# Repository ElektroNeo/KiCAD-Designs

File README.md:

# KiCAD-Designs
Useful KiCAD designs.

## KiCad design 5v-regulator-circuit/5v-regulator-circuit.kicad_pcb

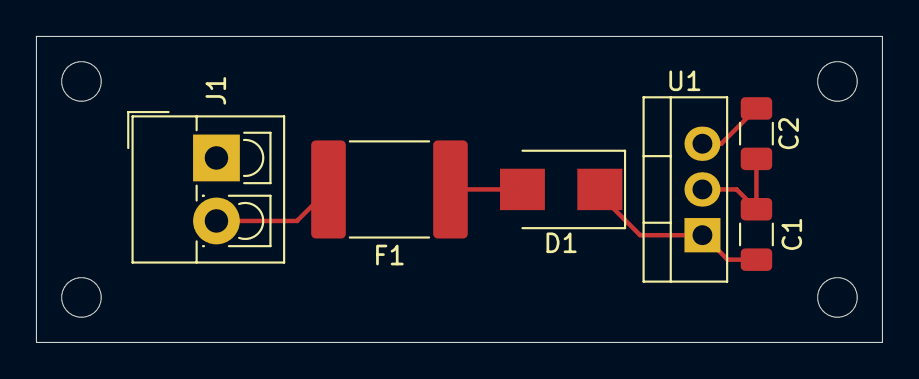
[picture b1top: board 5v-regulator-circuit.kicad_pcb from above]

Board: 2 copper layers, 47.0 x 17.0 mm, 6 parts (0 on the bottom side), 5 nets.

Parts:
C1: 0.33uF; C_1206_3216Metric
C2: 0.1uF; C_1206_3216Metric
D1: SS26-HT; D_SMB
F1: FSMD100; Fuse_2920_7451Metric
J1: Power In; TerminalBlock_4Ucon_1x02_P3.50mm_Vertical
U1: L7805; TO-220-3_Vertical

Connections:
+5V: C2.1, U1.3
GND: C1.2, C2.2, J1.1, U1.2
unnamed: C1.1, D1.1, U1.1
unnamed: D1.2, F1.1
unnamed: F1.2, J1.2

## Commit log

2021-01-01 Added 5V Regulator Circuit
2021-01-01 Added title block parameters.
